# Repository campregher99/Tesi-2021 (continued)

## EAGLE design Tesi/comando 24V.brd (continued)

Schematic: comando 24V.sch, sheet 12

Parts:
EN_GPO_H: STRIP_3
J_GPO/I2C_H1: 61202021621
U7: SN74LS244N; N20

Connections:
+5V: EN_GPO_H.1, U7.20 (VCC); also elsewhere on the board
GND: EN_GPO_H.3, J_GPO/I2C_H1.1, J_GPO/I2C_H1.2 (3), J_GPO/I2C_H1.3 (5), J_GPO/I2C_H1.4 (7), J_GPO/I2C_H1.5 (9), J_GPO/I2C_H1.6 (11), J_GPO/I2C_H1.7 (13), J_GPO/I2C_H1.8 (15), J_GPO/I2C_H1.9 (17), J_GPO/I2C_H1.10 (19), U7.10 (GND); also elsewhere on the board
I/O_3V3_GPIO1: J_GPO/I2C_H1.20; also elsewhere on the board
I/O_3V3_I2C_SCL: J_GPO/I2C_H1.18 (16); also elsewhere on the board
I/O_3V3_I2C_SDA: J_GPO/I2C_H1.19 (18); also elsewhere on the board
unnamed: EN_GPO_H.2, U7.1 (!1G), U7.19 (!G/2G)
OUT_3V3_GPO1_H: U7.8 (1A4); also elsewhere on the board
OUT_3V3_GPO2_H: U7.6 (1A3); also elsewhere on the board
OUT_3V3_GPO3_H: U7.4 (1A2); also elsewhere on the board
OUT_3V3_GPO4_H: U7.2 (1A1); also elsewhere on the board
OUT_3V3_GPO5_H: U7.13 (2A2); also elsewhere on the board
OUT_3V3_GPO6_H: U7.15 (2A3); also elsewhere on the board
OUT_3V3_GPO7_H: U7.17 (2A4); also elsewhere on the board
OUT_5V_GPO1_H: J_GPO/I2C_H1.11 (2), U7.12 (1Y4)
OUT_5V_GPO2_H: J_GPO/I2C_H1.12 (4), U7.14 (1Y3)
OUT_5V_GPO3_H: J_GPO/I2C_H1.13 (6), U7.16 (1Y2)
OUT_5V_GPO4_H: J_GPO/I2C_H1.14 (8), U7.18 (1Y1)
OUT_5V_GPO5_H: J_GPO/I2C_H1.15 (10), U7.7 (2Y2)
OUT_5V_GPO6_H: J_GPO/I2C_H1.16 (12), U7.5 (2Y3)
OUT_5V_GPO7_H: J_GPO/I2C_H1.17 (14), U7.3 (2Y4)

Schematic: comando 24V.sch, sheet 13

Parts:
J1, J2, J3, J4, J5, J6: 61201021621; CONN_61201021621_WRE

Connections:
I/O_M1_1: J4.1; also elsewhere on the board
I/O_M1_2: J4.2; also elsewhere on the board
I/O_M1_11: J4.3; also elsewhere on the board
I/O_M1_12: J4.4; also elsewhere on the board
I/O_M1_13: J4.5; also elsewhere on the board
I/O_M1_14: J4.6; also elsewhere on the board
I/O_M1_15: J4.7; also elsewhere on the board
I/O_M1_16: J4.8; also elsewhere on the board
I/O_M1_17: J4.9; also elsewhere on the board
I/O_M1_18: J4.10; also elsewhere on the board
I/O_M1_19: J5.1; also elsewhere on the board
I/O_M1_20: J5.2; also elsewhere on the board
I/O_M1_26: J5.3; also elsewhere on the board
I/O_M1_27: J5.4; also elsewhere on the board
I/O_M1_28: J5.5; also elsewhere on the board
I/O_M1_30: J5.6; also elsewhere on the board
I/O_M1_31: J5.7; also elsewhere on the board
I/O_M1_32: J5.8; also elsewhere on the board
I/O_M1_33: J5.9; also elsewhere on the board
I/O_M1_39: J5.10; also elsewhere on the board
I/O_M1_40: J6.1; also elsewhere on the board
I/O_M1_42: J6.2; also elsewhere on the board
I/O_M1_43: J6.3; also elsewhere on the board
I/O_M1_44: J6.4; also elsewhere on the board
I/O_M1_46: J6.5; also elsewhere on the board
I/O_M1_50: J6.6; also elsewhere on the board
I/O_M2_1: J1.1; also elsewhere on the board
I/O_M2_2: J1.2; also elsewhere on the board
I/O_M2_11: J1.3; also elsewhere on the board
I/O_M2_12: J1.4; also elsewhere on the board
I/O_M2_13: J1.5; also elsewhere on the board
I/O_M2_14: J1.6; also elsewhere on the board
I/O_M2_15: J1.7; also elsewhere on the board
I/O_M2_16: J1.8; also elsewhere on the board
I/O_M2_17: J1.9; also elsewhere on the board
I/O_M2_18: J1.10; also elsewhere on the board
I/O_M2_19: J2.1; also elsewhere on the board
I/O_M2_20: J2.2; also elsewhere on the board
I/O_M2_26: J2.3; also elsewhere on the board
I/O_M2_27: J2.4; also elsewhere on the board
I/O_M2_28: J2.5; also elsewhere on the board
I/O_M2_30: J2.6; also elsewhere on the board
I/O_M2_31: J2.7; also elsewhere on the board
I/O_M2_32: J2.8; also elsewhere on the board
I/O_M2_33: J2.9; also elsewhere on the board
I/O_M2_39: J2.10; also elsewhere on the board
I/O_M2_40: J3.1; also elsewhere on the board
I/O_M2_42: J3.2; also elsewhere on the board
I/O_M2_43: J3.3; also elsewhere on the board
I/O_M2_44: J3.4; also elsewhere on the board
I/O_M2_46: J3.5; also elsewhere on the board
I/O_M2_50: J3.6; also elsewhere on the board

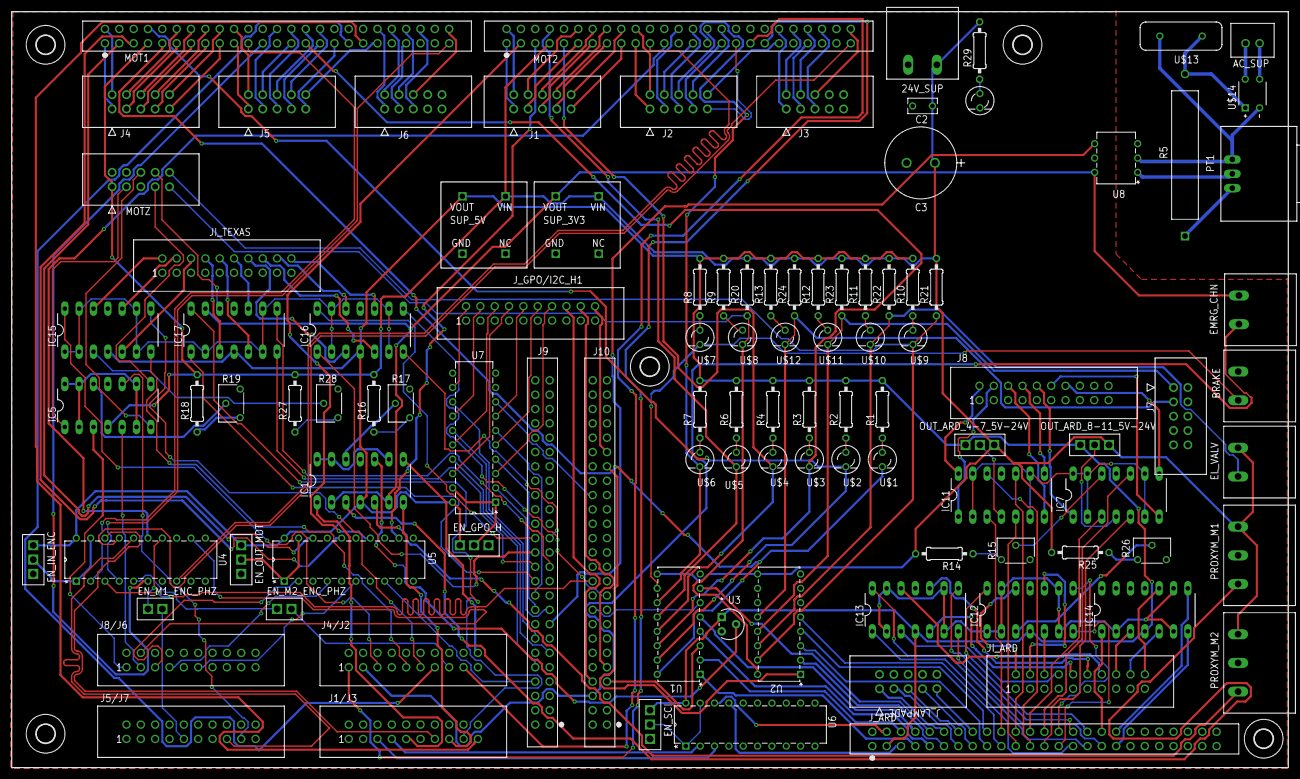
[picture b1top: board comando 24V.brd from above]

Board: 2 copper layers, 226.1 x 133.9 mm, 109 parts (0 on the bottom side), 242 nets.

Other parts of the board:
U$16, U$17, U$18, U$19, U$20: 3,3

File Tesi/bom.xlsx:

Qty | Value | Device | Package | Parts | Description | BUILT_BY | COPYRIGHT | DATASHEET | DATASHEET_URL | DESCRIPTION.1 | DIGI-KEY_PART_NUMBER | FAMILY_NAME | GENERIC_PART_NUMBER | INDUSTRY_STD_PKG_TYPE | MANUFACTURER | MANUFACTURER_PART_NUMBER | MF | MP | PACKAGE.1 | PACKAGE_DESIGNATOR | PIN_COUNT | POPULARITY | PURCHASE-URL | SOURCELIBRARY | SPICEPREFIX | VENDOR | Column1
12 | 200R | R-EU_0207/10 | 0207/10 | R1, R2, R3, R4, R6, R7, R8, R9, R10, R11, R12, R13 | RESISTOR, European symbol |  |  |  |  |  |  |  |  |  |  |  |  |  |  |  |  | 81 |  |  | R
1 | 2K | R-EU_0207/10 | 0207/10 | R29 | RESISTOR, European symbol |  |  |  |  |  |  |  |  |  |  |  |  |  |  |  |  | 81 |  |  | R
5 | 47k | R-EU_0207/10 | 0207/10 | R14, R16, R18, R25, R27 | RESISTOR, European symbol |  |  |  |  |  |  |  |  |  |  |  |  |  |  |  |  | 81 |  |  | R
5 | 4k7 | R-EU_0207/10 | 0207/10 | R20, R21, R22, R23, R24 | RESISTOR, European symbol |  |  |  |  |  |  |  |  |  |  |  |  |  |  |  |  | 81 |  |  | R
10 | 61201021621 | 61201021621 | CONN_61201021621_WRE | J1, J2, J3, J4, J5, J6, J7, J_LAMPADE, MOTZ_1, MOTZ_2 |  | EMA_Justin | Copyright (C) 2018 Accelerated Designs. All rights reserved |  |  |  |  |  |  |  |  | 61201021621 |  |  |  |  |  |  |  | WURTH_2019-10-22 |  | Wurth Electronics
8 | 61202021621 | 61202021621 | 61202021621 | J1/J3, J4/J2, J5/J7, J8, J8/J6, JI_ARD, JI_TEXAS, J_GPO/I2C_H1 | WR-BHD 2.54mm Male Box Header, 20 Pins=>Code : Con_WTB_BHD_2.54_Male_THT_WS_612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 |  |  |  |  | Connector Header Through Hole 20 position 0.100 (2.54mm) | 732-2096-ND |  |  |  |  |  | WÃ¼rth Elektronik | 61202021621 | None |  |  |  | https://pricing.snapeda.com/search/part/61202021621/?ref=eda
1 | B2B-XH-A(LF)(SN) | B2B-XH-A(LF)(SN) | CONN_B2B-XH-A(LF)(SN)_JST | AC_SUP |  | EMA_Cory | Copyright (C) 2018 Accelerated Designs. All rights reserved |  |  |  |  |  |  |  |  | B2B-XH-A(LF)(SN) |  |  |  |  |  |  |  | JST_2019-12-02 |  | JST
2 | BR30X | BR30X | BR30X | SUP_3V3, SUP_5V
1 | C0U12F | C0U12F | C0U12F | U$13
2 | CON_2F | CON_2F | CON_2F | 24V_SUP, EL_VALV
2 | CON_3F | CON_3F | CON_3F | PROXYM_M1, PROXYM_M2
1 | H11L1M | H11L1M | PDIP6-646BX_ONS | U8 |  | EMA_Justin | Copyright (C) 2018 Accelerated Designs. All rights reserved | https://www.onsemi.com/pub/Collateral/H11L3M-D.PDF |  |  |  |  |  |  |  | H11L1M |  |  |  |  |  |  |  | ON_Semiconductor_2020-01-13 |  | ON Semiconductor
1 | LED_ON | LED_TONDO | LED_TONDO | U$15
12 | LED_TONDO | LED_TONDO | LED_TONDO | U$1, U$2, U$3, U$4, U$5, U$6, U$7, U$8, U$9, U$10, U$11, U$12
12 | LM324N | LM324N | DIL14 | IC1, IC2, IC3, IC5, IC7, IC11, IC12, IC13, IC14, IC15, IC16, IC17 | OP AMP |  |  |  |  |  |  |  |  |  |  |  |  |  |  |  |  | 9
1 | MB6M-E3/45 | MB6M-E3/45 | DIP508W58P254L483H270Q4 | U$14
1 | OY104KE | OY104KE | RES_OY_OHM | R5 |  | EMA_UL_Team |  |  |  |  |  |  |  |  |  | OY104KE |  |  |  |  |  |  |  | Ohmite_2015_05_22 |  | Ohmite
1 | POT_2W_5K | POT_2W_5K | POT_2W_5K | PT1
5 | SBH11-PBPC-D25-ST-BK | SBH11-PBPC-D25-ST-BK | CONN_SBH11-PBPC-D25-ST-BK_SUL | J9, J10, J_ARD, MOT1, MOT2 |  | EMA_Cory | Copyright (C) 2018 Accelerated Designs. All rights reserved |  |  |  |  |  |  |  |  | SBH11-PBPC-D25-ST-BK |  |  |  |  |  |  |  | Sullins_2020-01-16 |  | Sullins
4 | SN74LS244N | SN74LS244N | N20 | U4, U5, U6, U7 |  |  |  |  | http://www.ti.com/lit/gpn/SN74LS244 | Octal Buffers And Line Drivers With 3-State Outputs |  | NON-INVERTING BUFFER/DRIVER | SN74LS244 | PDIP | Texas Instruments |  |  |  |  | N | 20
2 | STRIP_2 | STRIP_2 | STRIP_2 | EN_M1_ENC_PHZ, EN_M2_ENC_PHZ
6 | STRIP_3 | STRIP_3 | STRIP_3 | EN_GPO_H, EN_IN_ENC, EN_OUT_MOT, EN_SCI, OUT_ARD_4-7_5V-24V, OUT_ARD_8-11_5V-24V
1 | TEMP_ADJ | 64WR5KLF | RES3_64W_TTE | R17 |  |  | Copyright (C) 2016 Accelerated Designs. All rights reserved |  |  |  |  |  |  |  |  | 64WR5KLF |  |  |  |  |  |  |  | TTELECTRONICS_2018-04-10 |  | TT Electronics
1 | TMP37FT9Z | TMP37FT9Z | T_3_ADI | U3 |  | EMA_UL_Team |  |  |  |  |  |  |  |  |  | TMP37FT9Z |  |  |  |  |  |  |  | Analog_2012-01-01_9 |  | Analog Devices Inc
2 | ULN2003A | ULN2003A | DIP-16_STM | U1, U2 |  | EMA_UL_Team |  |  |  |  |  |  |  |  |  | ULN2003A |  |  |  |  |  |  |  | Update_to_database_2020-12-04 |  | STMicroelectronics
1 | VS_3V3_ADJ | 64WR5KLF | RES3_64W_TTE | R19 |  |  | Copyright (C) 2016 Accelerated Designs. All rights reserved |  |  |  |  |  |  |  |  | 64WR5KLF |  |  |  |  |  |  |  | TTELECTRONICS_2018-04-10 |  | TT Electronics
1 | VS_5v_ADJ | 64WR5KLF | RES3_64W_TTE | R15 |  |  | Copyright (C) 2016 Accelerated Designs. All rights reserved |  |  |  |  |  |  |  |  | 64WR5KLF |  |  |  |  |  |  |  | TTELECTRONICS_2018-04-10 |  | TT Electronics
1 | VS_ARD_ADJ | 64WR5KLF | RES3_64W_TTE | R26 |  |  | Copyright (C) 2016 Accelerated Designs. All rights reserved |  |  |  |  |  |  |  |  | 64WR5KLF |  |  |  |  |  |  |  | TTELECTRONICS_2018-04-10 |  | TT Electronics
1 | VS_EDGE_ADJ | 64WR5KLF | RES3_64W_TTE | R28 |  |  | Copyright (C) 2016 Accelerated Designs. All rights reserved |  |  |  |  |  |  |  |  | 64WR5KLF |  |  |  |  |  |  |  | TTELECTRONICS_2018-04-10 |  | TT Electronics

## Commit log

2021-03-05 init
2021-03-05 eagle
2021-03-09 09/03/2021
2021-03-12 12/03/2021
2021-03-12 FINE LAVORO MATTINA
2021-03-12 pomeriggio finito
2021-03-13 13/03/2021
2021-03-13 fine giornata
2021-03-15 fine schematico
2021-03-15 fine schematico parte 2
2021-03-16 16/03/2021
2021-03-20 20/03/2021 mattina
2021-03-23 23/03/2021 placing
2021-03-26 inizio routing
2021-03-28 28/03/2021
2021-03-30 30/03/2021 fine primo routing
2021-04-03 03/04/2021
2021-04-06 06/04/2021 revisione frassine
2021-04-08 08/04/2021 messo a posto i fori
2021-04-08 messo a posto i drill files
2021-04-10 10/04/2021
2021-04-10 10/04/2021 inizio libreria CCS
2021-04-11 sera
2021-04-13 13/04/2021 parser funziona
2021-04-14 14/04/2021 settaggi gerber file corretti
2021-04-15 15/04/2021 avanzamento parser
2021-04-21 21/04/2021 risolto problema dataEntry
    mi ero dimenticato di allocare la variabile queue a livello globale
2021-04-21 mi ero dimenticato di chiudere prima di pushare
2021-04-22 reader funziona testato parzialmente
2021-04-22 mi sono dimenticato di chiudere ccs
2021-04-23 creazione variabili extern fine cinematica
2021-04-27 27/04/2021 progressione traduzione in C
2021-05-11 11/05/2021 mattina
2021-05-12 debug ccs Cinematica
2021-05-16 inizio risoluzione inclusione
2021-05-17 risolta circolarità
2021-07-16 risoluzione problema nella counicazione seriale
    Una volta che sorgeva un messaggio sbagliato i successivi erano sbagliati.
    Mancava l'azzeramento di i oltre alla variabile step
